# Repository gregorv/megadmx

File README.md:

# megadmx
An ATmega88 based LED dimmer, strobe and fog controller.

For a small project I needed an DMX controller for a 30W-70W white LED stroboscope, a length of RGB LED tape and a relay controlling a Eurolite N10 fog machine. The circutry is based on an ATmega88 controller (hence the repository name), with cheap
FETs for dimming and a beefy FET for the strobe. Cheap 24V 3A and 12V 2A switching power supplies from ebay power the device.

## DMX Channels
The controller uses 7 DMX channels. The starting address can be set with software or a 5 pin jumper header. Therefore, without firmware flashing only 32 different addresses are possible. :/

| Channel | Function                                |
| :-----: | :-------------------------------------- |
| 1       | Tape Dimmer 0-255                       |
| 2       | Tape Red 0-255                          |
| 3       | Tape Green 0-255                        |
| 4       | Tape Blue  0-255                        |
| 5       | Tape Strobe Frequency 1-255, 0 off      |
| 6       | LED Power Strobe Frequency 1-255, 0 off |
| 7       | Fog Off 0-126, Fog On 127-255           |

## Hardware Description
The mainboard is powered with +12V over a two pin connector. The supply current is used to light the LED tape. A 7805 generates the voltage for the microprocessor. A standard SP485 IC is used as DMX interface.

The PCB is designed to be home-etchable with the photo-transfer method. The PCB size can be _significantly_ reduced if a proper plated 2-layer layout is used.

### LED Tape Connection
A four pin connector is used for connecting a standard 12V LED tape with common anode. The pin layout follows the standard cabling order for this kind of tape.

| Pin | Function |
| :-: | -------- |
| 1   | +12 V    |
| 2   | Green    |
| 3   | Red      |
| 4   | Blue     |

### Power Strobe Connection
The power LED strobe circuit is a IRF540N Power-MOSFET switching a screw terminal input to ground. Connect a power LED low-side equiped with a suitable power supply (read: constant current / current limited). Note: the LED flashes when the circuit is turned on, because the FET driving ciruit invertes the logic state of the processor pin. This is a nice visual feedback that the device is switched on.

### Fog Machine Connection
We use a Eurolite N10 smoke machine. It is very cheap (less than 40€), the remote control switches mains voltages for the fluid pump, making it very simple to interface the machine with a simple relay. Note that part of the circuit is live on mains voltage, use the N10 control only if you know about the risks and neccessary safety procedures.

## Software Description

Peter Flery UART library for DMX reception.

TIMER0 overflow interrupt generates 3 channel PWM for LED tape.

TIMER2 in CTC interrupt generates strobe for tape and power LED.

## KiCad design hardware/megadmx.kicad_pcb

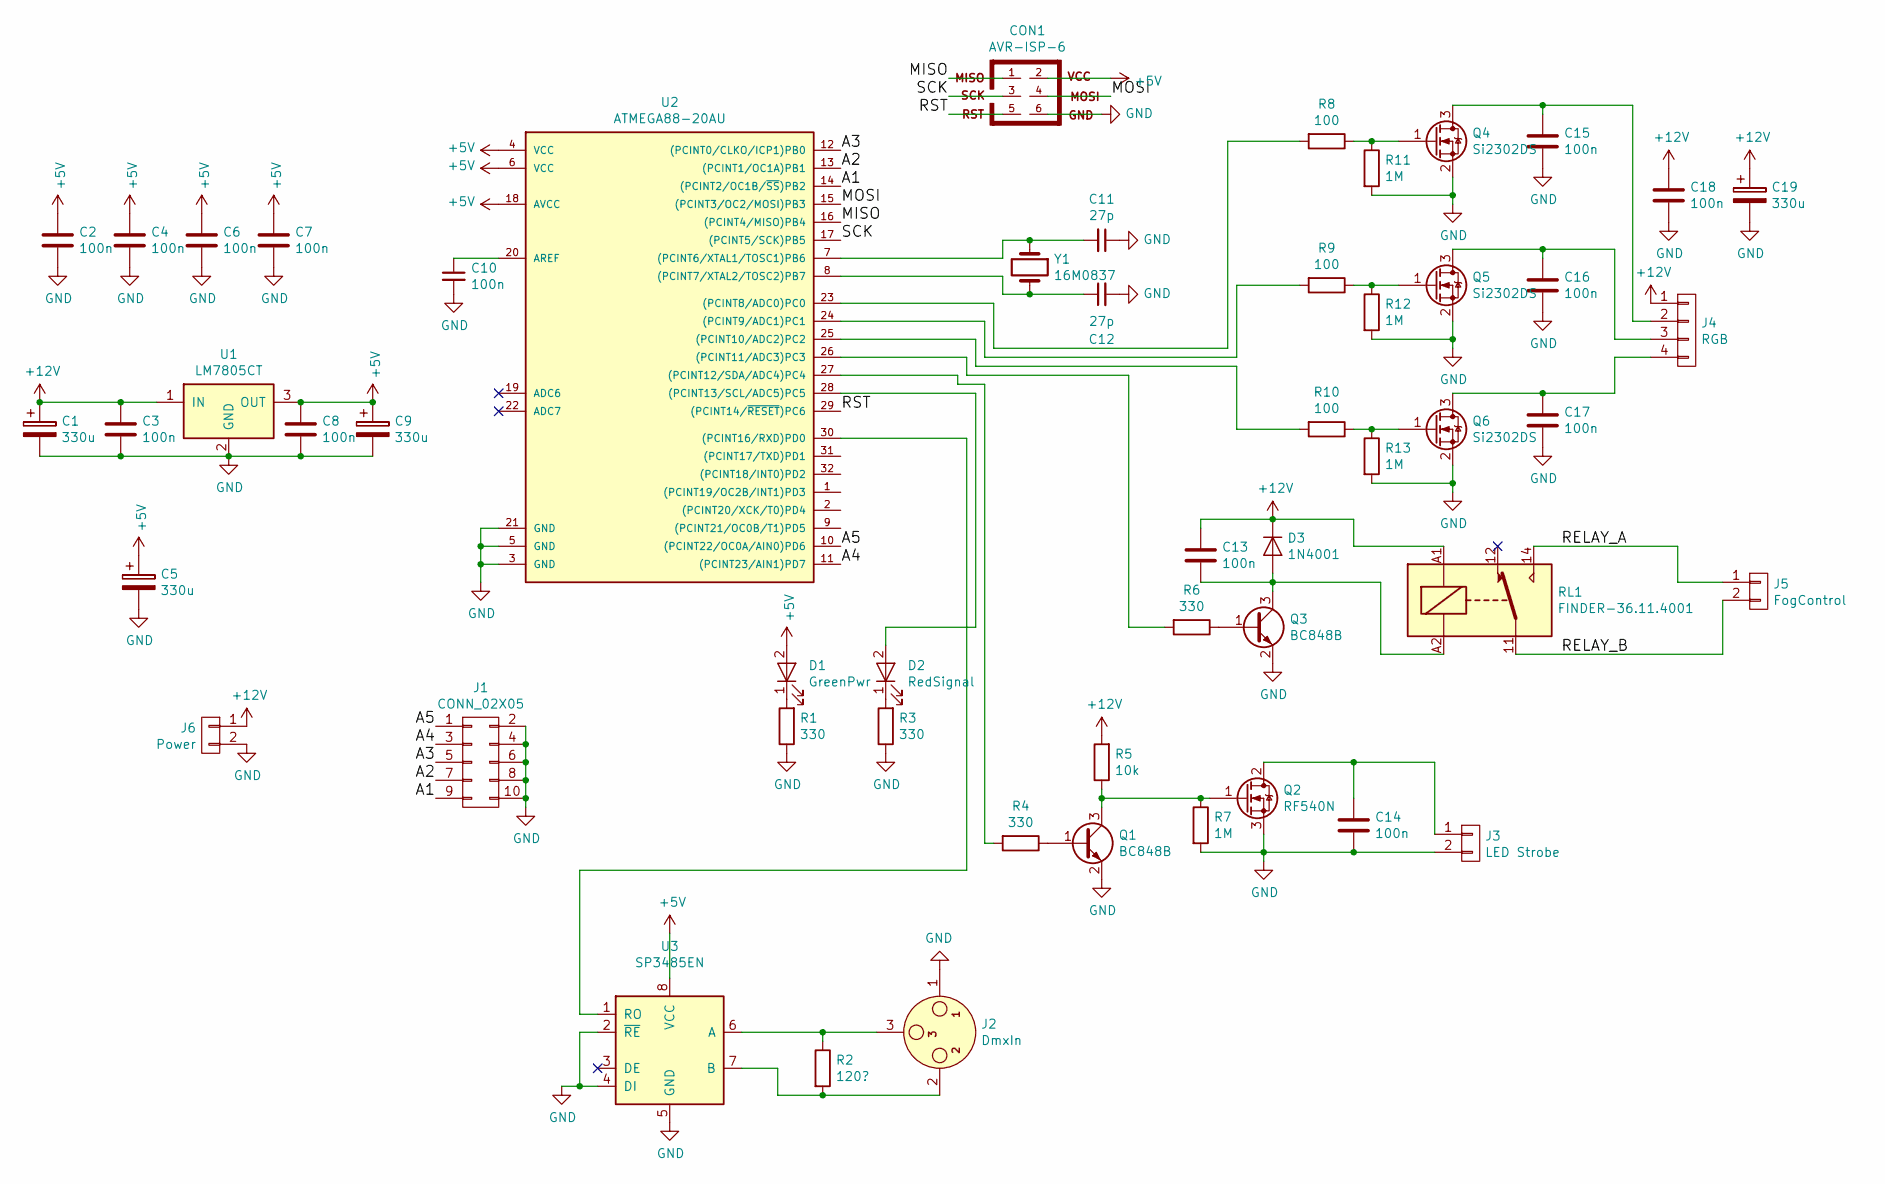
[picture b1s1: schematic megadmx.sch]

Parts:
C1, C5, C9, C19: 330u; CP_Elec_8x10
C2, C3, C4, C6, C7, C8, C10, C13, C14, C15, C16, C17, C18: 100n; C_0603_HandSoldering
C11, C12: 27p; C_0603_HandSoldering
CON1: AVR-ISP-6; Pin_Header_Straight_2x03_Pitch2.54mm
D1: GreenPwr; LED_D5.0mm
D2: RedSignal; LED_D5.0mm
D3: 1N4001; D_DO-35_SOD27_P5.08mm_Vertical_KathodeUp
J1: CONN_02X05; Pin_Header_Angled_2x05_Pitch2.54mm
J2: DmxIn; XLR_NC3_MAH
J3: LED Strobe; TerminalBlock_Pheonix_MKDS1.5-2pol
J4: RGB; JST_EH_B04B-EH-A_04x2.50mm_Straight
J5: FogControl; JST_EH_B02B-EH-A_02x2.50mm_Straight
J6: Power; JST_EH_B02B-EH-A_02x2.50mm_Straight
Q1, Q3: BC848B; SOT-23
Q2: RF540N; TO-220_Neutral123_Vertical_LargePads
Q4, Q5, Q6: Si2302DS; SOT-23
R1, R3, R4, R6: 330; R_0603_HandSoldering
R2: 120?; R_0603_HandSoldering
R5: 10k; R_0603_HandSoldering
R7, R11, R12, R13: 1M; R_0603_HandSoldering
R8, R9, R10: 100; R_0603_HandSoldering
RL1: FINDER-36.11.4001; Relay_Finder_series36
U1: LM7805CT; TO-220
U2: ATMEGA88-20AU; TQFP-32_7x7mm_Pitch0.8mm
U3: SP3485EN; SOIC-8_3.9x4.9mm_Pitch1.27mm
Y1: 16M0837; Crystal_SMD_HC49-SD

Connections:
+5V: C2.1, C4.1, C5.1, C6.1, C7.1, C8.1, C9.1, CON1.2, D1.2 (A), U1.3 (OUT), U2.4 (VCC), U2.6 (VCC), U2.18 (AVCC), U3.8 (VCC)
+12V: C1.1, C3.1, C13.1, C18.1, C19.1, D3.1 (K), J4.1, J6.1, R5.2, RL1.A1, U1.1 (IN)
/A1: J1.9, U2.14 ((PCINT2/OC1B/~SS~)PB2)
/A2: J1.7, U2.13 ((PCINT1/OC1A)PB1)
/A3: J1.5, U2.12 ((PCINT0/CLKO/ICP1)PB0)
/A4: J1.3, U2.11 ((PCINT23/AIN1)PD7)
/A5: J1.1, U2.10 ((PCINT22/OC0A/AIN0)PD6)
/MISO: CON1.1, U2.16 ((PCINT4/MISO)PB4)
/MOSI: CON1.4, U2.15 ((PCINT3/OC2/MOSI)PB3)
/RELAY_A: J5.1, RL1.14
/RELAY_B: J5.2, RL1.11
/RST: CON1.5, U2.29 ((PCINT14/~RESET~)PC6)
/SCK: CON1.3, U2.17 ((PCINT5/SCK)PB5)
GND: C1.2, C2.2, C3.2, C4.2, C5.2, C6.2, C7.2, C8.2, C9.2, C10.2, C11.1, C12.2, C14.1, C15.2, C16.2, C17.2, C18.2, C19.2, CON1.6, J1.2, J1.4, J1.6, J1.8, J1.10, J2.1, J3.2, J6.2, Q1.2 (E), Q2.3 (S), Q3.2 (E), Q4.2 (S), Q5.2 (S), Q6.2 (S), R1.1, R3.1, R7.2, R11.2, R12.2, R13.2, U1.2 (GND), U2.3 (GND), U2.5 (GND), U2.21 (GND), U3.2 (~RE~), U3.4 (DI), U3.5 (GND)
unnamed: C10.1, U2.20 (AREF)
unnamed: C11.2, U2.7 ((PCINT6/XTAL1/TOSC1)PB6), Y1.1
unnamed: C12.1, U2.8 ((PCINT7/XTAL2/TOSC2)PB7), Y1.2
unnamed: C13.2, D3.2 (A), Q3.3 (C), RL1.A2
unnamed: C14.2, J3.1, Q2.2 (D)
unnamed: C15.1, J4.2, Q4.3 (D)
unnamed: C16.1, J4.3, Q5.3 (D)
unnamed: C17.1, J4.4, Q6.3 (D)
unnamed: D1.1 (K), R1.2
unnamed: D2.1 (K), R3.2
unnamed: D2.2 (A), U2.28 ((PCINT13/SCL/ADC5)PC5)
unnamed: J2.2, R2.2, U3.7 (B)
unnamed: J2.3, R2.1, U3.6 (A)
unnamed: Q1.1 (B), R4.1
unnamed: Q1.3 (C), Q2.1 (G), R5.1, R7.1
unnamed: Q3.1 (B), R6.1
unnamed: Q4.1 (G), R8.1, R11.1
unnamed: Q5.1 (G), R9.1, R12.1
unnamed: Q6.1 (G), R10.1, R13.1
unnamed: R4.2, U2.27 ((PCINT12/SDA/ADC4)PC4)
unnamed: R6.2, U2.26 ((PCINT11/ADC3)PC3)
unnamed: R8.2, U2.23 ((PCINT8/ADC0)PC0)
unnamed: R9.2, U2.24 ((PCINT9/ADC1)PC1)
unnamed: R10.2, U2.25 ((PCINT10/ADC2)PC2)
unnamed: U2.30 ((PCINT16/RXD)PD0), U3.1 (RO)

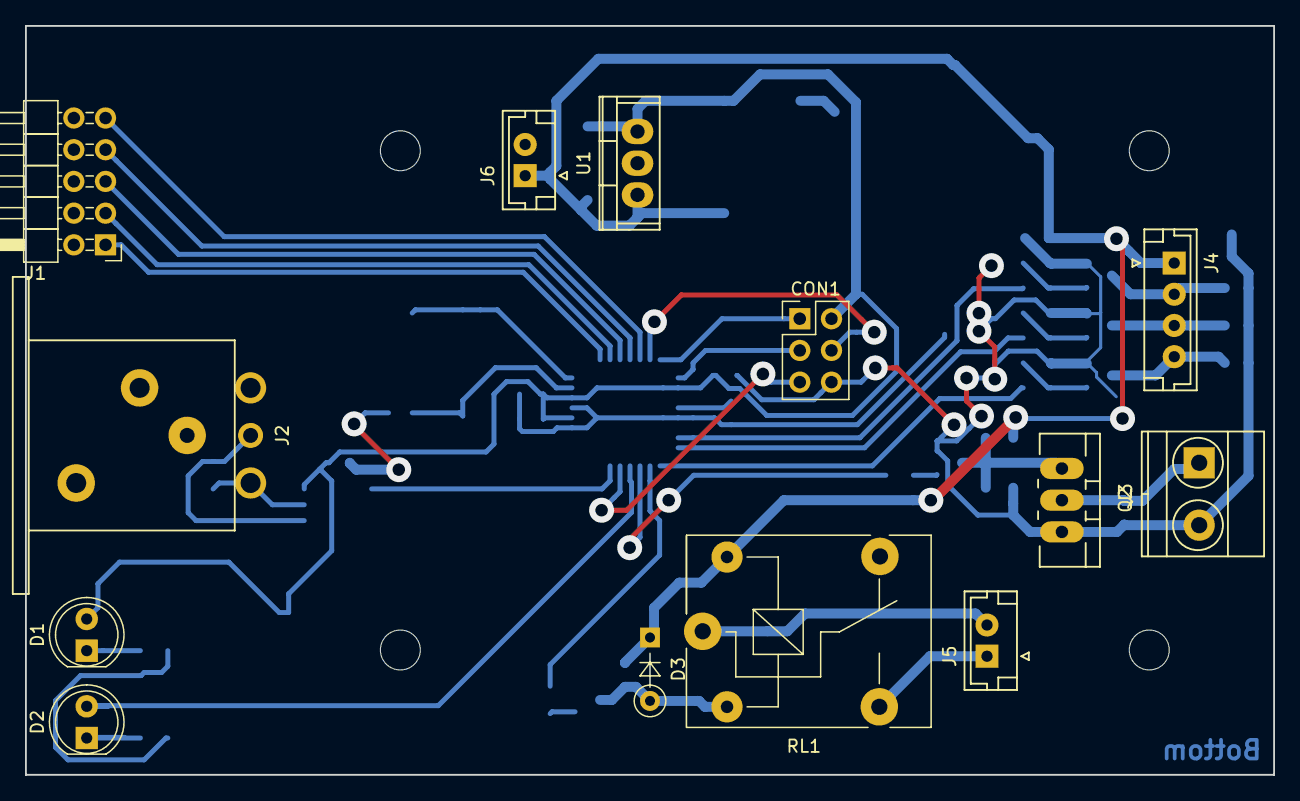
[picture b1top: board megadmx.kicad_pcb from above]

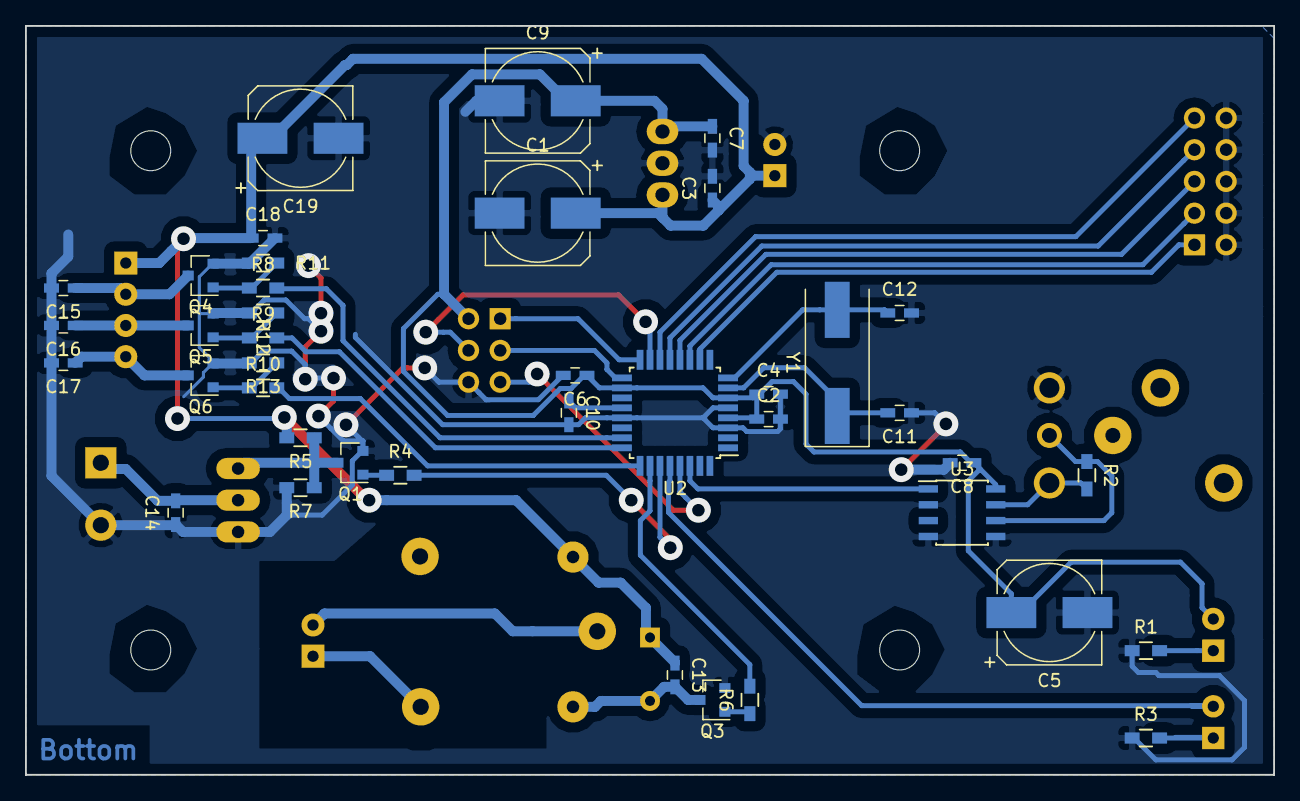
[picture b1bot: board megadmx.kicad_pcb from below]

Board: 2 copper layers, 100.0 x 60.0 mm, 53 parts (40 on the bottom side), 39 nets.

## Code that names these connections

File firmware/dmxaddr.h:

/*  MegaDMX – ATmega8 DMX Firmware for Toilet-Control
    Copyright (C) 2017 Gregor Vollmer <git@dynamic-noise.net>

    This program is free software: you can redistribute it and/or modify
    it under the terms of the GNU General Public License as published by
    the Free Software Foundation, either version 3 of the License, or
    (at your option) any later version.

    This program is distributed in the hope that it will be useful,
    but WITHOUT ANY WARRANTY; without even the implied warranty of
    MERCHANTABILITY or FITNESS FOR A PARTICULAR PURPOSE.  See the
    GNU General Public License for more details.

    You should have received a copy of the GNU General Public License
    along with this program.  If not, see <http://www.gnu.org/licenses/>.
*/
#ifndef DMX_ADDR_H
#define DMX_ADDR_H

void dmx_addr_init(void);
uint16_t dmx_addr_read(void);

/* DMX Address Pins */
#define DMX_ADDR_4_PIN	PB2
#define DMX_ADDR_4_IN	PINB
#define DMX_ADDR_4_OUT	PORTB
#define DMX_ADDR_4_DDR	DDRB

#define DMX_ADDR_3_PIN	PB1
#define DMX_ADDR_3_IN	PINB
#define DMX_ADDR_3_OUT	PORTB
#define DMX_ADDR_3_DDR	DDRB

#define DMX_ADDR_2_PIN	PB0
#define DMX_ADDR_2_IN	PINB
#define DMX_ADDR_2_OUT	PORTB
#define DMX_ADDR_2_DDR	DDRB

#define DMX_ADDR_1_PIN	PD7
#define DMX_ADDR_1_IN	PIND
#define DMX_ADDR_1_OUT	PORTD
#define DMX_ADDR_1_DDR	DDRD

#define DMX_ADDR_0_PIN	PD6
#define DMX_ADDR_0_IN	PIND
#define DMX_ADDR_0_OUT	PORTD
#define DMX_ADDR_0_DDR	DDRD

#endif

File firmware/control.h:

/*  MegaDMX – ATmega8 DMX Firmware for Toilet-Control
    Copyright (C) 2017 Gregor Vollmer <git@dynamic-noise.net>

    This program is free software: you can redistribute it and/or modify
    it under the terms of the GNU General Public License as published by
    the Free Software Foundation, either version 3 of the License, or
    (at your option) any later version.

    This program is distributed in the hope that it will be useful,
    but WITHOUT ANY WARRANTY; without even the implied warranty of
    MERCHANTABILITY or FITNESS FOR A PARTICULAR PURPOSE.  See the
    GNU General Public License for more details.

    You should have received a copy of the GNU General Public License
    along with this program.  If not, see <http://www.gnu.org/licenses/>.
*/

#ifndef CONTROL_H
#define CONTROL_H

#define COLOR_LED_RED	PC1
#define COLOR_LED_GREEN	PC2
#define COLOR_LED_BLUE	PC0
#define COLOR_LED_IN	PINC
#define COLOR_LED_OUT	PORTC
#define COLOR_LED_DDR	DDRC

#define STROBE_LED_PIN	PC4
#define STROBE_LED_IN	PINC
#define STROBE_LED_OUT	PORTC
#define STROBE_LED_DDR	DDRC

#define FOG_RELAY_PIN	PD2
#define FOG_RELAY_IN	PIND
#define FOG_RELAY_OUT	PORTD
#define FOG_RELAY_DDR	DDRD

void control_init(void);
void control_ledstrip(uint8_t dimmer, uint8_t red, uint8_t green, uint8_t blue, uint8_t strobe);
void control_strobe(uint8_t strobe);
void control_fog_on(void);
void control_fog_off(void);

#endif

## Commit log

2017-06-20 Initial version of megadmx firmware
2017-06-20 Added optimized KiCad hardware layout
2017-06-20 Added licenses and authors
2017-06-20 Added more rules to gitignore
